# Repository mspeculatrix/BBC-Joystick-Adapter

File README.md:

# BBC Joystick Adapter

WORK IN PROGRESS

Simple breakout board for an RJ45 socket that allows you to wire up an analogue joystick and connect it to the BBC Micro or BBC Master via an Ethernet cable and my BBC Joystick adapter.

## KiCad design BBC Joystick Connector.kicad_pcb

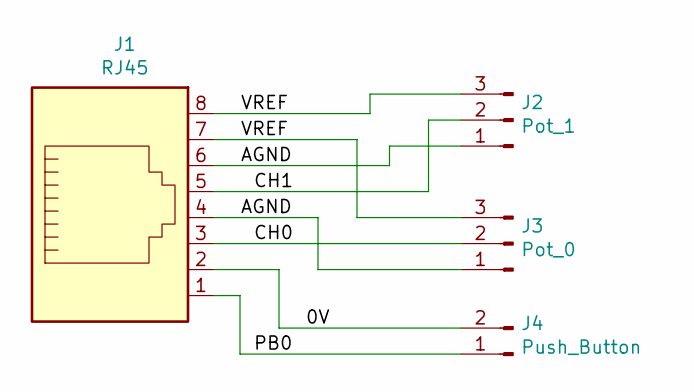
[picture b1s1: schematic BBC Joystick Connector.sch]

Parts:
J1: RJ45; RJ45_Eth
J2: Pot_1; Pin_Header_Angled_1x03
J3: Pot_0; Pin_Header_Angled_1x03
J4: Push_Button; Pin_Header_Angled_1x02

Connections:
/0V: J1.2, J4.2
/AGND: J1.4, J1.6, J2.1, J3.1
/CH0: J1.3, J3.2
/CH1: J1.5, J2.2
/PB0: J1.1, J4.1
/VREF: J1.7, J1.8, J2.3, J3.3

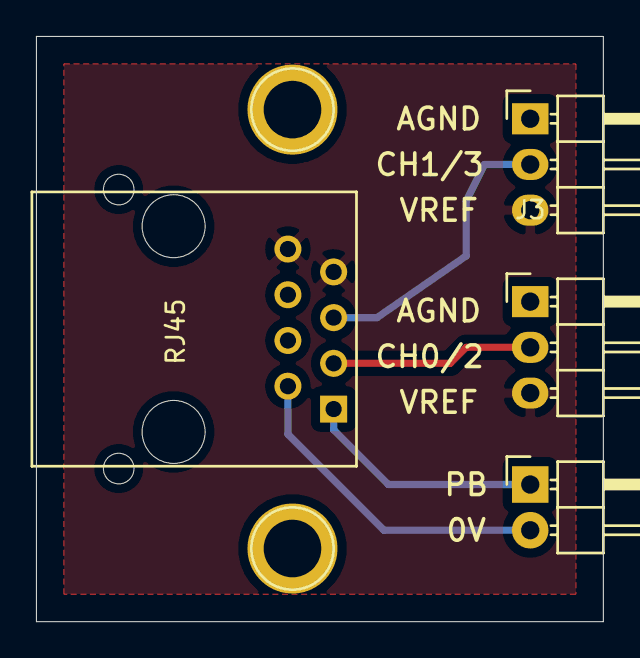
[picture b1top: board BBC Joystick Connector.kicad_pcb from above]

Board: 2 copper layers, 31.5 x 32.5 mm, 4 parts (0 on the bottom side), 6 nets.
